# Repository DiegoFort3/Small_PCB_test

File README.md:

# Small_PCB_test
A test to learn how to integrate Github and KiCad 

Created to leran how to use Git, Github and KiCad

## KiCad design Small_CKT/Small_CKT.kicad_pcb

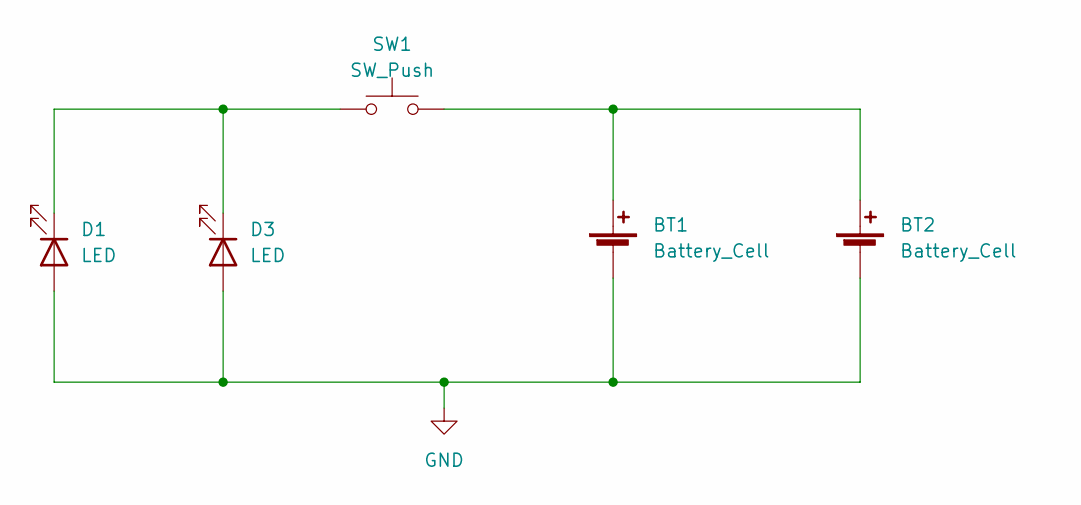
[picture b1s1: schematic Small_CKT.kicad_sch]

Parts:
BT1, BT2: Battery_Cell; Molex_KK-254_AE-6410-02A_1x02_P2.54mm_Vertical
D1, D3: LED; LED_0805_2012Metric_Pad1.15x1.40mm_HandSolder
SW1: SW_Push; SW_Push_1P1T_NO_CK_KMR2

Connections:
GND: BT1.2 (-), BT2.2 (-), D1.2 (A), D3.2 (A)
unnamed: BT1.1 (+), BT2.1 (+), SW1.2
unnamed: D1.1 (K), D3.1 (K), SW1.1

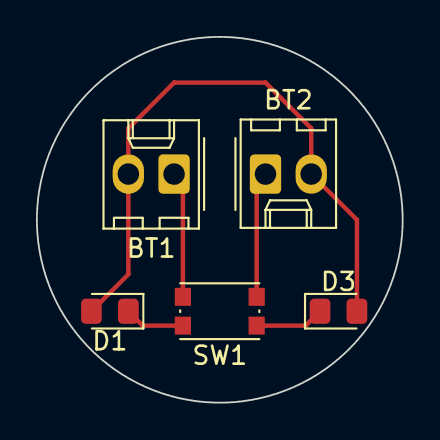
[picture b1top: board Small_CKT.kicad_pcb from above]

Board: 2 copper layers, 20.3 x 20.3 mm, 5 parts (0 on the bottom side), 3 nets.

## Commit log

2023-05-20 Schematic added
2023-05-20 Added footprints to LED, SW, and battery
2023-05-20 Placed compenents in layout
2023-05-20 Added traces in layout
2023-05-20 Create README.md
    Added readme
2023-05-20 SMD footprint Layout and schematic edition
